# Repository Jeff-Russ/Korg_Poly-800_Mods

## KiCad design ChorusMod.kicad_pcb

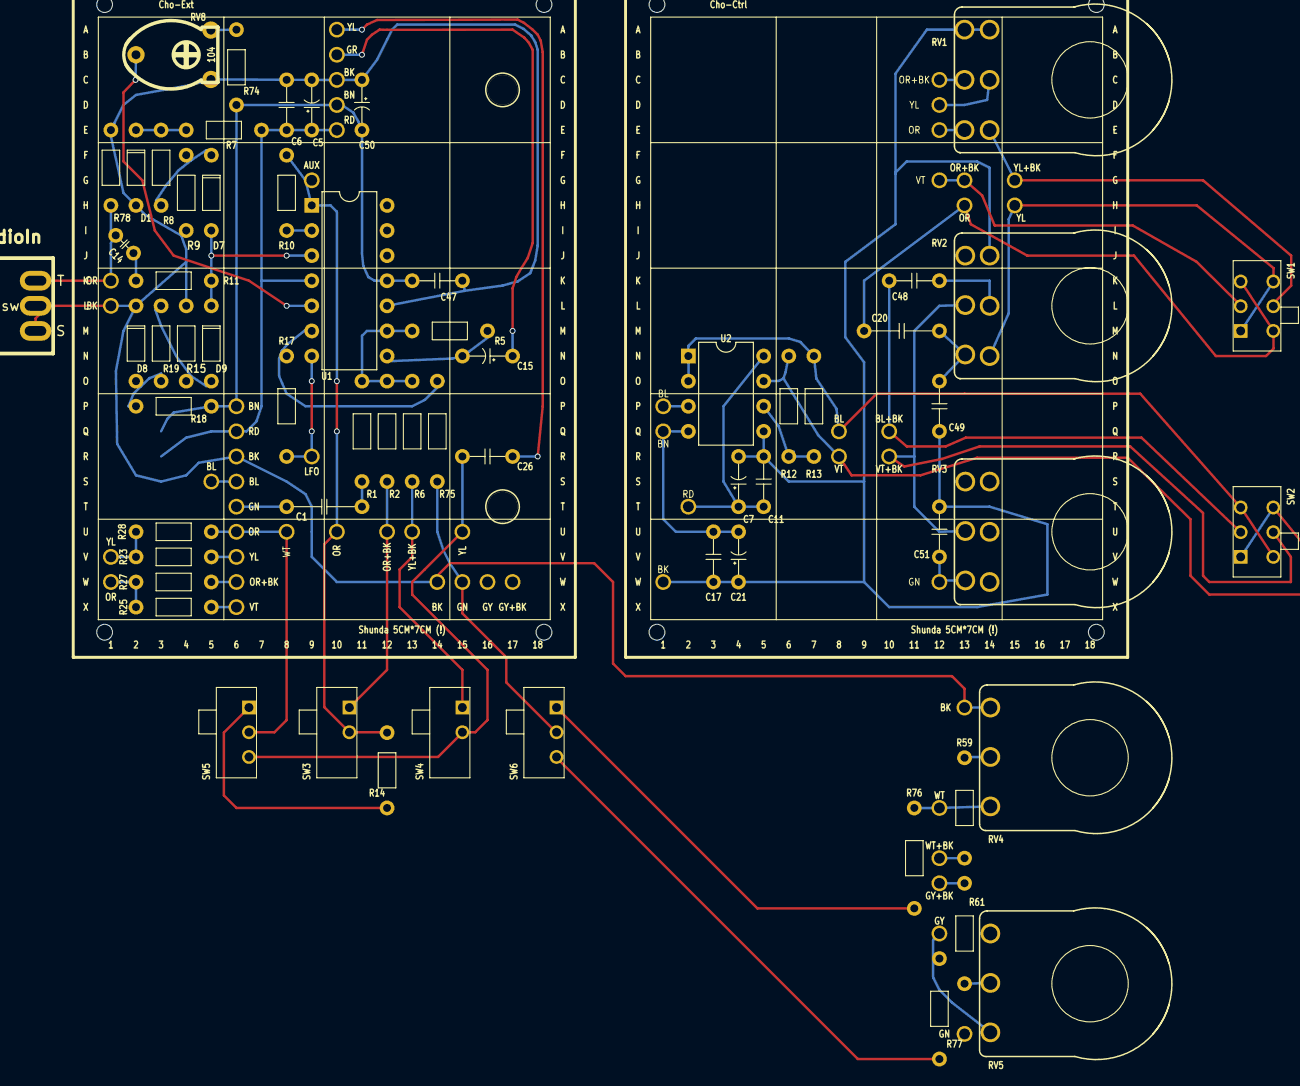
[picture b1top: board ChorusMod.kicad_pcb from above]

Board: 2 copper layers, 118 parts (0 on the bottom side), 80 nets.

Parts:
C1: 0.1µ; 300Mil_TH_C
C5, C50: 1µ; 200Mil_TH_CP
C6, C11, C17, C47, C48, C49, C51: 0.1µ; 200Mil_TH_C
C7, C21: 1µ; 200Mil_TH_CP_no3D
C14: 2.2µ; 100Mil_TH_C
C15: 10µ; 200Mil_TH_CP
C20: 1µ; 300Mil_TH_C_no3D
C26: 2.2µ; 200Mil_TH_C
D1, D8: 2v2; 300Mil_TH_Diode
D7, D9: 1N4148; 300Mil_TH_Diode
Drill1, Drill2: 3mm_DrillHole
J1: AuxAudioIn; TS_Jack_Switched_Generic
J1.11: WT; Conn_Female_Dupont-1_Val
J1.12, J2.3: BK; Conn_Female_Dupont-1_Val
J1.13, J2.6: OR; Conn_Female_Dupont-1_Val
J1.14: YL; Conn_Female_Dupont-1
J1.15, J2.8: OR+BK; Conn_Female_Dupont-1_Val
J1.16: YL+BK; Conn_Female_Dupont-1_Val
J1.17, J2.5: GN; Conn_Female_Dupont-1_Val
J2.1: BN; Conn_Female_Dupont-1_Val
J2.2: RD; Conn_Female_Dupont-1_Val
J2.4: BL; Conn_Female_Dupont-1_Val
J2.7: YL; Conn_Female_Dupont-1_Val
J2.9: VT; Conn_Female_Dupont-1_Val
JAUX.1: BK; Conn_Female_Dupont-1_Val
JAUX.2: OR; Conn_Female_Dupont-1_Val
JAUX.3: AUX; Conn_Female_Dupont-1_Val
JLFO.1: LFO; Conn_Female_Dupont-1_Val
PCB1: Shunda 5CM*7CM (!); perfboard_24x18_Shunda_misprint
R1, R6: 22K; 400Mil_TH_Resistor
R2: 33K; 400Mil_TH_Resistor
R5: 22K; 300Mil_TH_Resistor
R7, R18: 1K; 300Mil_TH_Resistor
R8, R9, R15, R19: 470; 300Mil_TH_Resistor
R10, R11: 5.1K; 300Mil_TH_Resistor
R12, R13: 47K; 400Mil_TH_Resistor
R14: 15K; 300Mil_TH_Resistor
R17, R77: 1.5M; 400Mil_TH_Resistor
R23, R25: 18K; 300Mil_TH_Resistor
R27, R28: 33K; 300Mil_TH_Resistor
R59: 10K; 400Mil_TH_Resistor
R61: 4.7K; 400Mil_TH_Resistor
R74: 1M; 300Mil_TH_Resistor
R75: 1M; 400Mil_TH_Resistor
R76: 220K; 400Mil_TH_Resistor
R78: 470K; 300Mil_TH_Resistor
RV1: DUAL_B250K; 400x100Mil_TH_Pot_Dual_FaceUp_FlipGangs
RV2: DUAL_B100K; 400x100Mil_TH_Pot_Dual_FaceUp
RV3: B10K; 400x500Mil_TH_Pot_reinfoced_FaceUp
RV4: B100K; 400Mil_TH_Pot_FaceUp
RV5: B1M; 400Mil_TH_Pot_FaceUp
RV8: 104; trimmer_extended_wiper
SW1: ChoFilterPan; TH_DPDT_Angled
SW2: ChoFbInv; TH_DPDT_Angled
SW3: AuxToChorus; TH_SPST_Angled
SW4: KorgToChorus; TH_SPST_Angled
SW5: DrySource; TH_SPDT_Angled
SW6: LFO2 Sel; TH_SPDT_Angled
U1: TL084; 300Mil_DIP14
U2: NJM4556; 300Mil_DIP8
W1, W2.7, W8: YL; TH_Wire_Val
W1.1: GY+BK; Conn_Female_Dupont-1
W1.2: GY; Conn_Female_Dupont-1
W1.5: BK; Conn_Female_Dupont-1_Val
W1.6: GN; Conn_Female_Dupont-1_Val
W1.7: GY; Conn_Female_Dupont-1_Val
W1.8: GY+BK; Conn_Female_Dupont-1_Val
W1.9: WT; Conn_Female_Dupont-1_Val
W1.10: WT+BK; Conn_Female_Dupont-1_Val
W2: GR; TH_Wire_Val
W2.1, W4: BN; TH_Wire_Val
W2.2, W5: RD; TH_Wire_Val
W2.3, W3: BK; TH_Wire_Val
W2.4, W6: BL; TH_Wire_Val
W2.5: GN; TH_Wire_Val
W2.6, W7: OR; TH_Wire_Val
W2.8: OR+BK; TH_Wire_Val
W2.9: VT; TH_Wire_Val
W.Inv.I1: VT; TH_Wire
W.Inv.I2: BL; TH_Wire
W.Inv.O1: BL+BK; TH_Wire
W.Inv.O2: VT+BK; TH_Wire
W.Pan.I1: YL; TH_Wire
W.Pan.I2: OR; TH_Wire
W.Pan.O1: OR+BK; TH_Wire
W.Pan.O2: YL+BK; TH_Wire

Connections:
/HPWet: RV2.6, W.Pan.I1.1
/LPWet: C20.2, W.Pan.I2.1
/PreHP: C48.1, W.Inv.O1.1
/PreLP: RV2.2, RV3.2, W.Inv.O2.1
/Squ: W1.2.2, W1.7.2
/WetInv: R12.1, U2.7, W.Inv.I1.1
unnamed: C1.1, J2.5.1
unnamed: C1.2, R1.2
unnamed: C5.1, C6.2, J2.2.1, R7.2, U1.4, W5.1
unnamed: C7.1, C11.1, U2.8, W2.2.1
unnamed: C7.2, C11.2, C17.2, C21.1, C49.2, C51.2, RV1.1, RV1.4, RV2.4, U2.5, W2.3.1
unnamed: C14.1, R11.1
unnamed: C14.2, JAUX.2.1, R78.1
unnamed: C15.1, W2.1
unnamed: C15.2, R5.2, U1.8
unnamed: C17.1, C21.2, U2.4, W2.1.1
unnamed: C20.1, C49.1, RV2.3
unnamed: C26.1, J1.14.1
unnamed: C26.2, W1.1
unnamed: C47.1, C50.2, J2.1.1, R18.2, R74.2, U1.11, W4.1
unnamed: C5.2, C6.1, C47.2, C50.1, D1.2, D8.1, J1.12.1, J2.3.1, JAUX.1.1, R9.1, R15.2, R78.2, RV8.1, U1.10, W3.1
unnamed: C48.2, RV2.5
unnamed: C51.1, RV3.3, W2.5.1
unnamed: D1.1, R7.1, R8.1
unnamed: D7.1, R8.2, R9.2
unnamed: D7.2, D9.1, R11.2, U1.3
unnamed: D8.2, R18.1, R19.1
unnamed: D9.2, R15.1, R19.2
unnamed: J1.1, JAUX.2.2
unnamed: J1.2, J1.3, JAUX.1.2
unnamed: J1.11.1, J2.6.1, R28.2
unnamed: J1.11.2, SW5.2
unnamed: J1.12.2, W1.5.2
unnamed: J1.13.1, JAUX.3.1, R10.2, U1.1
unnamed: J1.13.2, R14.2, SW3.2
unnamed: J1.14.2, SW4.2, SW5.3
unnamed: J1.15.1, R2.2
unnamed: J1.15.2, SW3.1
unnamed: J1.16.1, R6.2
unnamed: J1.16.2, SW4.1
unnamed: J1.17.1, R75.1
unnamed: J1.17.2, SW6.2
unnamed: J2.4.1, W6.1
unnamed: J2.7.1, R23.2
unnamed: J2.8.1, R27.2
unnamed: J2.9.1, R25.2
unnamed: JLFO.1.1, R17.1, U1.7
unnamed: R1.1, R2.1, R5.1, R6.1, U1.9
unnamed: R10.1, U1.2
unnamed: R12.2, R13.2, U2.6
unnamed: R13.1, U2.1, U2.2, W.Inv.I2.1
unnamed: R14.1, SW5.1
unnamed: R17.2, R75.2, U1.6
unnamed: R23.1, R28.1, W8.1
unnamed: R25.1, R27.1, W7.1
unnamed: R59.1, RV4.2
unnamed: R59.2, W1.10.1
unnamed: R61.1, RV5.2
unnamed: R61.2, W1.1.1, W1.8.1
unnamed: R74.1, RV8.3
unnamed: R76.1, RV4.3, W1.9.1
unnamed: R76.2, SW6.1
unnamed: R77.1, SW6.3
unnamed: R77.2, RV5.3, W1.2.1, W1.7.1
unnamed: RV1.2, W2.7.1
unnamed: RV1.3, W.Pan.O2.1
unnamed: RV1.5, W2.8.1
unnamed: RV1.6, W2.6.1
unnamed: RV4.1, W1.5.1
unnamed: RV8.2, U1.5
unnamed: SW1.1, SW1.6, W.Pan.I1.2
unnamed: SW1.2, W.Pan.O1.2
unnamed: SW1.3, SW1.4, W.Pan.I2.2
unnamed: SW1.5, W.Pan.O2.2
unnamed: SW2.1, SW2.6, W.Inv.I1.2
unnamed: SW2.2, W.Inv.O1.2
unnamed: SW2.3, SW2.4, W.Inv.I2.2
unnamed: SW2.5, W.Inv.O2.2
unnamed: U2.3, W2.4.1
unnamed: W2.9.1, W.Pan.O1.1

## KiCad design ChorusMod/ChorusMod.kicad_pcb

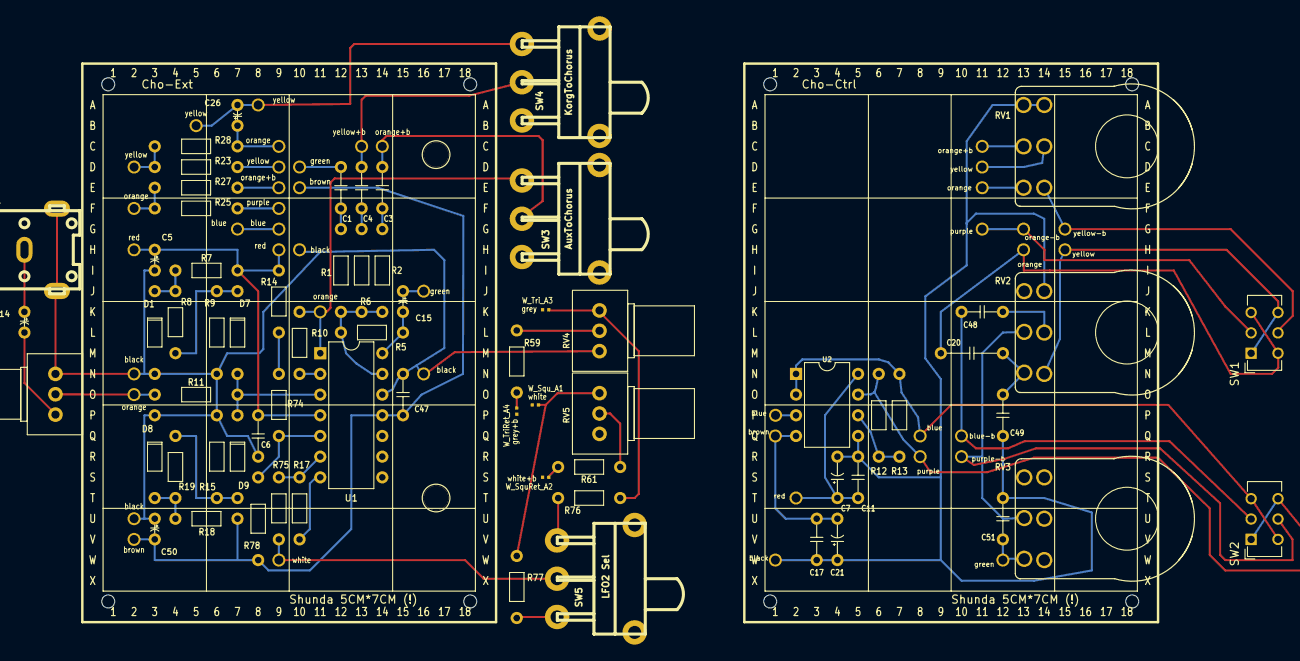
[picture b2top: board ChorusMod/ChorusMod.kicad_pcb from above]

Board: 2 copper layers, 111 parts (0 on the bottom side), 78 nets.

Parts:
C1, C3, C4: 47n; 200Mil_TH_C
C5, C26, C50: 1µ; 100Mil_TH_CP
C6, C11, C17, C47, C48, C49, C51: 0.1µ; 200Mil_TH_C
C7, C21: 1µ; 200Mil_TH_CP_no3D
C14, C15: 10µ; 100Mil_TH_CP
C20: 1µ; 300Mil_TH_C_no3D
D1, D8: 2v2; 400Mil_TH_Diode
D7, D9: 1N4148; 400Mil_TH_Diode
Drill1, Drill2: 3mm_DrillHole
J1: AuxAudioIn; rca_red
P_+A_A4: red; TH_Wire_Val
P_+A_A6: red; TH_Wire
P_+A_B6: red; Conn_Female_Dupont-1_Val
P_-A_A3: brown; TH_Wire_Val
P_-A_A8: brown; TH_Wire
P_-A_B8: brown; Conn_Female_Dupont-1_Val
P_Aux_P2, P_Aux_P7: orange; Conn_Female_Dupont-1_Val
P_Aux_P3: orange+b; Conn_Female_Dupont-1_Val
P_DryCP_A1: orange; TH_Wire
P_DryCP_B1: orange; Conn_Female_Dupont-1_Val
P_DryR_A3: orange+b; TH_Wire
P_DryR_B3: orange+b; Conn_Female_Dupont-1_Val
P_DryRet_A2: green; TH_Wire_Val
P_Dry_A1: yellow; TH_Wire_Val
P_FB_A9: green; TH_Wire
P_FB_B9: green; Conn_Female_Dupont-1_Val
P_GND_A5: black; TH_Wire_Val
P_GND_A7: black; TH_Wire
P_GND_B7: black; Conn_Female_Dupont-1_Val
P_GND_P5, P_GND_P8: black; Conn_Female_Dupont-1_Val
P_HP_P7: blue-b; TH_Wire
P_KS_P1: yellow; Conn_Female_Dupont-1_Val
P_KS_P4: yellow+b; Conn_Female_Dupont-1_Val
P_LFO_P6: white; Conn_Female_Dupont-1_Val
P_LP_P8: purple-b; TH_Wire
P_L_A8: yellow; TH_Wire_Val
P_OnHP_P5: blue; TH_Wire
P_OnLP_P6: purple; TH_Wire
P_OnL_P4: yellow; TH_Wire
P_OnR_P3: orange; TH_Wire
P_R_A7: orange; TH_Wire_Val
P_WetL_A2: yellow; TH_Wire
P_WetL_B2: yellow; Conn_Female_Dupont-1_Val
P_WetL_P2: yellow-b; TH_Wire
P_WetR_A4: purple; TH_Wire
P_WetR_B4: purple; Conn_Female_Dupont-1_Val
P_WetR_P1: orange-b; TH_Wire
P_Wet_A5: blue; TH_Wire
P_Wet_A6: blue; TH_Wire_Val
P_Wet_B5: blue; Conn_Female_Dupont-1_Val
R1, R6: 22K; 400Mil_TH_Resistor
R2, R27, R28: 33K; 400Mil_TH_Resistor
R5: 22K; 300Mil_TH_Resistor
R7, R18: 1K; 300Mil_TH_Resistor
R8, R19: 470; 300Mil_TH_Resistor
R9, R15: 470; 400Mil_TH_Resistor
R10: 5.1K; 300Mil_TH_Resistor
R11: 5.1K; 400Mil_TH_Resistor
R12, R13: 47K; 400Mil_TH_Resistor
R14: 100K; 300Mil_TH_Resistor
R17, R77: 1.5M; 300Mil_TH_Resistor
R23, R25: 18K; 400Mil_TH_Resistor
R59: 10K; 300Mil_TH_Resistor
R61: 4.7K; 300Mil_TH_Resistor
R74: 12K; 300Mil_TH_Resistor
R75: 1M; 300Mil_TH_Resistor
R76: 220K; 300Mil_TH_Resistor
R78: 100K; 400Mil_TH_Resistor
RV1: DUAL_B250K; 400x100Mil_TH_Pot_Dual_FaceUp_FlipGangs
RV2: DUAL_B100K; 400x100Mil_TH_Pot_Dual_FaceUp
RV3: B10K; 400x500Mil_TH_Pot_reinfoced_FaceUp
RV4, RV6: B100K; Pot_TH_Mini_pcbEdge
RV5: B1M; Pot_TH_Mini_pcbEdge
SW1: ChoFilterPan; SW_CuK_JS202011AQN_DPDT_Angled
SW2: ChoFbInv; SW_CuK_JS202011AQN_DPDT_Angled
SW3: AuxToChorus; switch_mfp116dg-ra
SW4: KorgToChorus; switch_mfp116dg-ra
SW5: LFO2 Sel; switch_mfp116dg-ra
U1: TL084; 300Mil_DIP14
U2: NJM4556; 300Mil_DIP8
W_SquRet_A2: white+b; Wire_Ref-Val
W_Squ_A1: white; Wire_Ref-Val
W_TriRet_A4: grey+b; Wire_Ref-Val
W_Tri_A3: grey; Wire_Ref-Val

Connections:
/+A: C7.1, C11.1, P_+A_A6.1, U2.8
/-A: C17.1, C21.2, P_-A_A8.1, U2.4
/FB: C51.1, P_FB_A9.1, RV3.3
/GND: C7.2, C11.2, C17.2, C21.1, C49.2, C51.2, P_GND_A7.1, RV1.1, RV1.4, RV2.4, U2.5
/HPWet: P_OnL_P4.1, RV2.6
/LPWet: C20.2, P_OnR_P3.1
/PreHP: C48.1, P_HP_P7.1
/PreLP: P_LP_P8.1, RV2.2, RV3.2
/ToChorus: C15.2, R5.2, U1.14
/Wet: P_OnHP_P5.1, R13.1, U2.1, U2.2
/WetInv: P_OnLP_P6.1, R12.1, U2.7
unnamed: C1.1, P_FB_B9.1
unnamed: C1.2, R1.2
unnamed: C3.1, P_Aux_P3.1
unnamed: C3.2, R2.1
unnamed: C4.1, P_KS_P4.1
unnamed: C4.2, R6.2
unnamed: C5.1, C6.2, P_+A_A4.1, P_+A_B6.1, R7.2, R14.1, U1.4
unnamed: C14.1, J1.1
unnamed: C14.2, RV6.3
unnamed: C15.1, P_DryRet_A2.1
unnamed: C20.1, C49.1, RV2.3
unnamed: C26.1, P_DryCP_B1.1, R28.2
unnamed: C26.2, P_Dry_A1.1, P_KS_P1.1
unnamed: C47.1, C50.2, P_-A_A3.1, P_-A_B8.1, R18.2, R78.2, U1.11
unnamed: C5.2, C6.1, C47.2, C50.1, D1.2, D8.1, P_GND_A5.1, P_GND_B7.1, P_GND_P5.1, P_GND_P8.1, R9.1, R15.2, U1.12
unnamed: C48.2, RV2.5
unnamed: D1.1, R7.1, R8.1
unnamed: D7.1, R8.2, R9.2
unnamed: D7.2, D9.1, R11.2, U1.3
unnamed: D8.2, R18.1, R19.1
unnamed: D9.2, R15.1, R19.2
unnamed: J1.2, P_GND_P8.2, RV6.1
unnamed: P_Aux_P2.1, R10.2, U1.1
unnamed: P_Aux_P2.2, SW3.3
unnamed: P_Aux_P3.2, SW3.2
unnamed: P_Aux_P7.1, R11.1
unnamed: P_Aux_P7.2, RV6.2
unnamed: P_DryCP_A1.1, RV1.6
unnamed: P_DryR_A3.1, RV1.5
unnamed: P_DryR_B3.1, R27.2
unnamed: P_GND_P5.2, RV4.1
unnamed: P_HP_P7.2, SW2.2
unnamed: P_KS_P1.2, SW4.3
unnamed: P_KS_P4.2, SW4.2
unnamed: P_LFO_P6.1, R75.1
unnamed: P_LFO_P6.2, SW5.2
unnamed: P_LP_P8.2, SW2.5
unnamed: P_L_A8.1, R23.1, R28.1
unnamed: P_OnHP_P5.2, SW2.3, SW2.4
unnamed: P_OnLP_P6.2, SW2.1, SW2.6
unnamed: P_OnL_P4.2, SW1.1, SW1.6
unnamed: P_OnR_P3.2, SW1.3, SW1.4
unnamed: P_R_A7.1, R25.1, R27.1
unnamed: P_WetL_A2.1, RV1.2
unnamed: P_WetL_B2.1, R23.2
unnamed: P_WetL_P2.1, RV1.3
unnamed: P_WetL_P2.2, SW1.5
unnamed: P_WetR_A4.1, P_WetR_P1.1
unnamed: P_WetR_B4.1, R25.2
unnamed: P_WetR_P1.2, SW1.2
unnamed: P_Wet_A5.1, U2.3
unnamed: P_Wet_A6.1, P_Wet_B5.1
unnamed: R1.1, R2.2, R5.1, R6.1, U1.13
unnamed: R10.1, U1.2
unnamed: R12.2, R13.2, U2.6
unnamed: R14.2, R74.1
unnamed: R17.1, U1.7
unnamed: R17.2, R75.2, U1.6
unnamed: R59.1, RV4.2
unnamed: R59.2, W_TriRet_A4.2
unnamed: R61.1, RV5.2
unnamed: R61.2, W_SquRet_A2.2
unnamed: R74.2, R78.1, U1.5
unnamed: R76.1, RV4.3, W_Tri_A3.2
unnamed: R76.2, SW5.3
unnamed: R77.1, SW5.1
unnamed: R77.2, RV5.3, W_Squ_A1.2

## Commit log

2017-11-02 remove old schematics
2017-11-04 Moved independent boards to sub-projects
2017-11-04 renamed sub-project so paths are shorter.
2017-11-04 add some .png schematics
2017-11-05 assign footprints, start pcb
2017-11-09 further work on pcb
2017-11-09 previously forgot to save before commit
2017-11-15 save-point before some experimental pcb markings
2017-11-19 just a save-point
2017-11-22 routine save-point
2017-11-23 chorus mods are mostly done, sans error proofing
2018-01-18 Chorus mod effectively complete sans some clean up
2018-01-18 Chorus mod effectively done sans some cleanup
2018-01-18 restructure to make chorus mod be repo root
2018-01-18 restructuring done; next comes documentation
2018-04-01 save point after modding my Korg. Next: replace wire colors with meaningful labels others can follow
